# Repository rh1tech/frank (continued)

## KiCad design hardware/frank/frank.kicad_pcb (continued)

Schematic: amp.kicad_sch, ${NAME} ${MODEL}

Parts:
C25, C30, C35: 1u; C_0805_2012Metric
C26, C27, C28, C32, C33: 10u; C_0805_2012Metric
C29, C34: 100n; C_0805_2012Metric
C31: 10u; CP_Radial_D4.0mm_P1.50mm
C36: 100u; C_Radial_D6.3mm_P2.50mm
R50, R52: 2K; R_0805_2012Metric
R51, R53, R54, R55, R56, R57, R58, R61, R65: 10K; R_0805_2012Metric
R59, R60: 47K; R_0805_2012Metric
R62: 100R; R_0805_2012Metric
R63, R64: 20K; R_0805_2012Metric
U9: PAM8403D; SOP-16_P1.27mm; Mouser Part Number 700-MAX232CSE
U10: LM358; SO-8

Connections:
/AMP_L: C26.1, R51.1; also elsewhere on the board
/AMP_R: C27.1, R53.1; also elsewhere on the board
/Audio/AMP_OUTL: C32.2, R63.2; also elsewhere on the board
/Audio/AMP_OUTR: C33.2, R64.2; also elsewhere on the board
/Audio/AMP_PAM_OUTL_M: U9.3 (-OUTL); also elsewhere on the board
/Audio/AMP_PAM_OUTL_P: U9.1 (+OUT_L); also elsewhere on the board
/Audio/AMP_PAM_OUTR_M: U9.14 (-OUT_R); also elsewhere on the board
/Audio/AMP_PAM_OUTR_P: U9.16 (+OUT_R); also elsewhere on the board
/MONO_L: C25.1, R50.1, R51.2; also elsewhere on the board
/MONO_R: C30.1, R52.1, R53.2; also elsewhere on the board
/SHND: R65.2, U9.12 (SHND); also elsewhere on the board
GND: C28.1, C29.2, C31.2, C34.1, C35.2, C36.2, R50.2, R52.2, R55.1, R63.1, R64.1, U9.2 (PGND), U9.11 (GND), U9.15 (PGND), U10.4 (V-); also elsewhere on the board
unnamed: C25.2, R56.2
unnamed: C26.2, R57.2
unnamed: C27.2, R58.2
unnamed: C30.2, R61.2
unnamed: C32.1, R59.1, U10.7
unnamed: C33.1, R60.1, U10.1
unnamed: R56.1, U9.7 (INL)
unnamed: R61.1, U9.10 (INR)
unnamed: C29.1, U9.8 (VREF)
unnamed: C28.2, R54.1, R55.2, U10.3 (+), U10.5 (+)
unnamed: R58.1, R60.2, U10.2 (-)
unnamed: R57.1, R59.2, U10.6 (-)
unnamed: C31.1, C34.2, R54.2, R62.2, U10.8 (V+)
VBUS: C35.1, C36.1, R62.1, R65.1, U9.4 (PVDD), U9.5 (MUTE), U9.6 (VDD), U9.13 (PVDD); also elsewhere on the board

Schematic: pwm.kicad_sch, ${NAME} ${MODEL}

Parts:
C20, C21: 47n; C_0805_2012Metric
R39, R41: 10K; R_0805_2012Metric
R40, R42, R43, R44: 2K; R_0805_2012Metric
R45, R46: 1K; R_0805_2012Metric

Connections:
/PGPIO9: R43.1, R44.1; also elsewhere on the board
/PGPIO10: R46.2; also elsewhere on the board
/PGPIO11: R45.2; also elsewhere on the board
/PWM_L: R41.2, R42.1; also elsewhere on the board
/PWM_R: R39.2, R40.1; also elsewhere on the board
GND: C20.2, C21.2, R40.2, R42.2; also elsewhere on the board
unnamed: C20.1, R39.1, R43.2, R46.1
unnamed: C21.1, R41.1, R44.2, R45.1

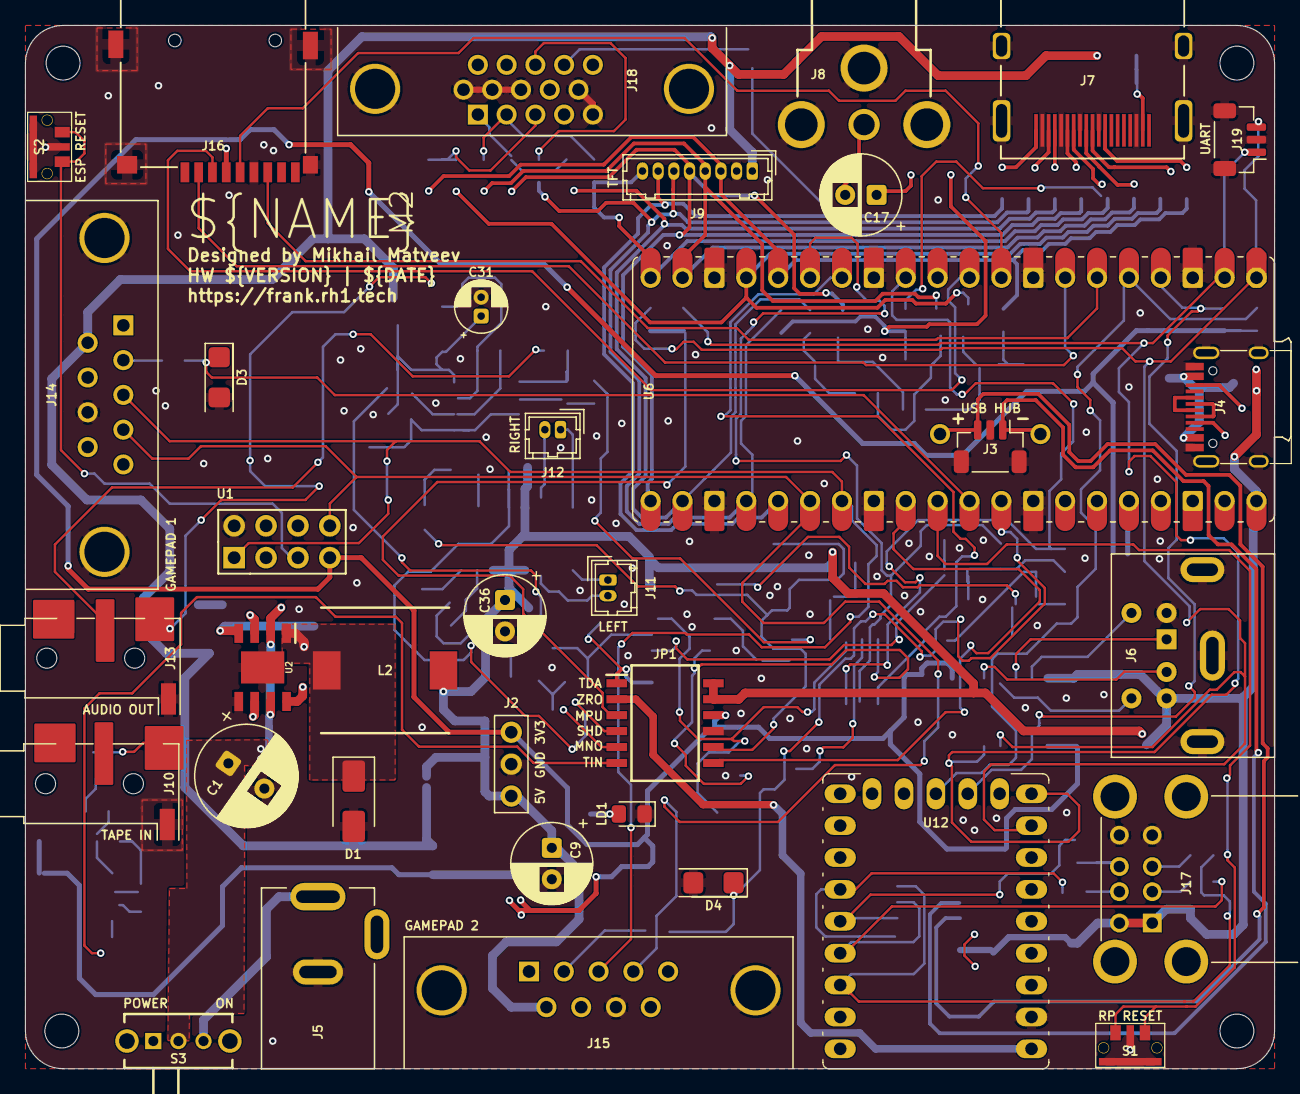
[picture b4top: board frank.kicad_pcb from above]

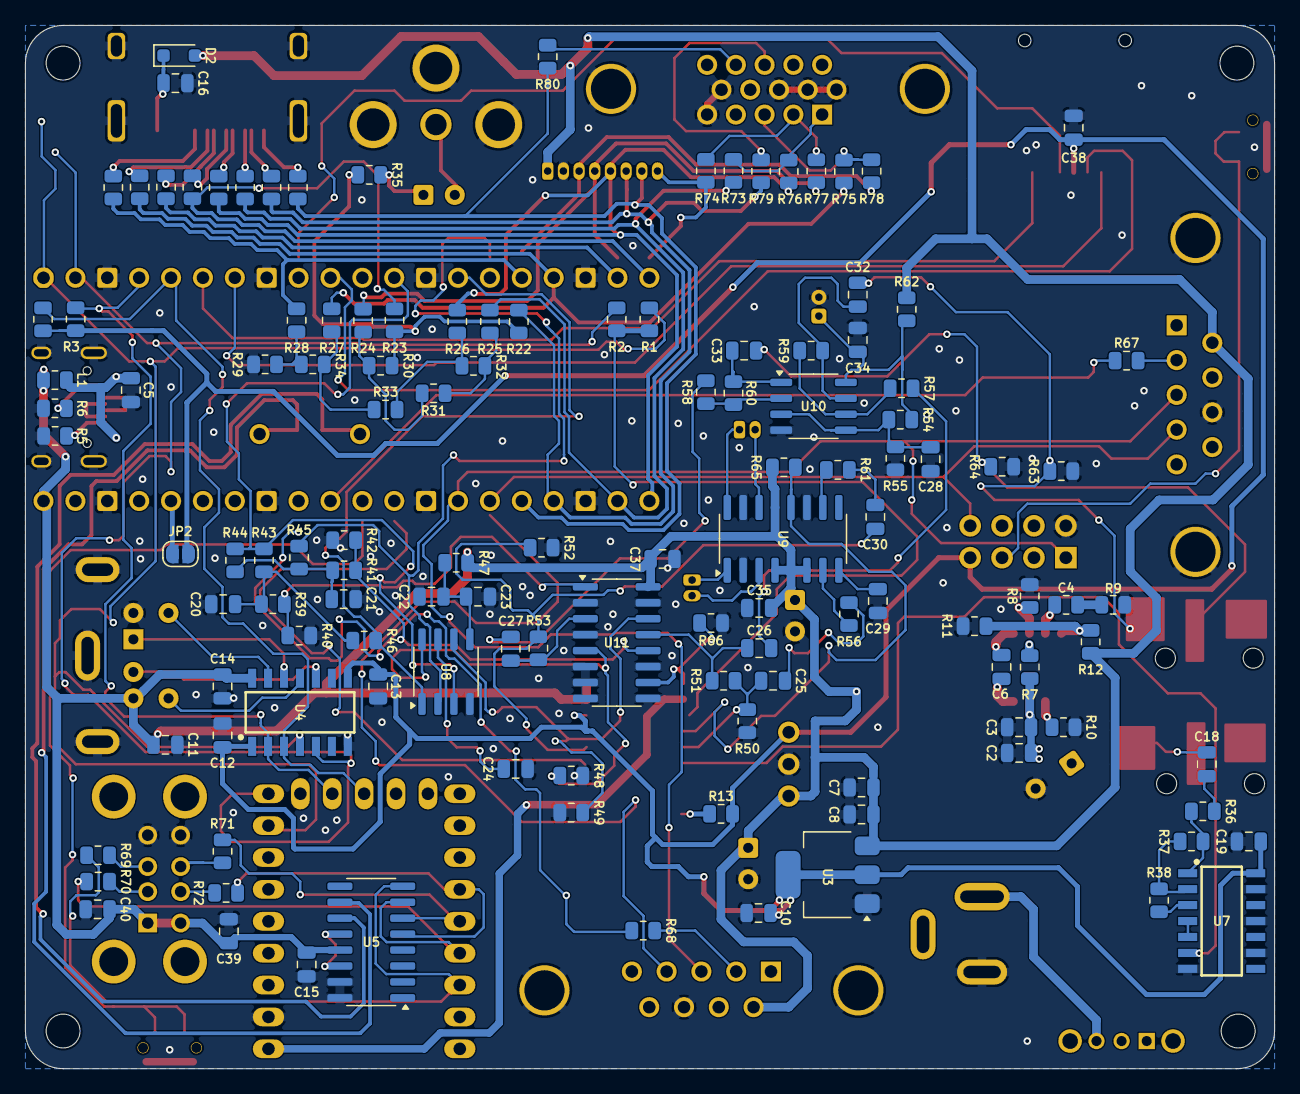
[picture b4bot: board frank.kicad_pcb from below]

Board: 2 copper layers, 99.5 x 83.1 mm, 166 parts (126 on the bottom side), 126 nets.

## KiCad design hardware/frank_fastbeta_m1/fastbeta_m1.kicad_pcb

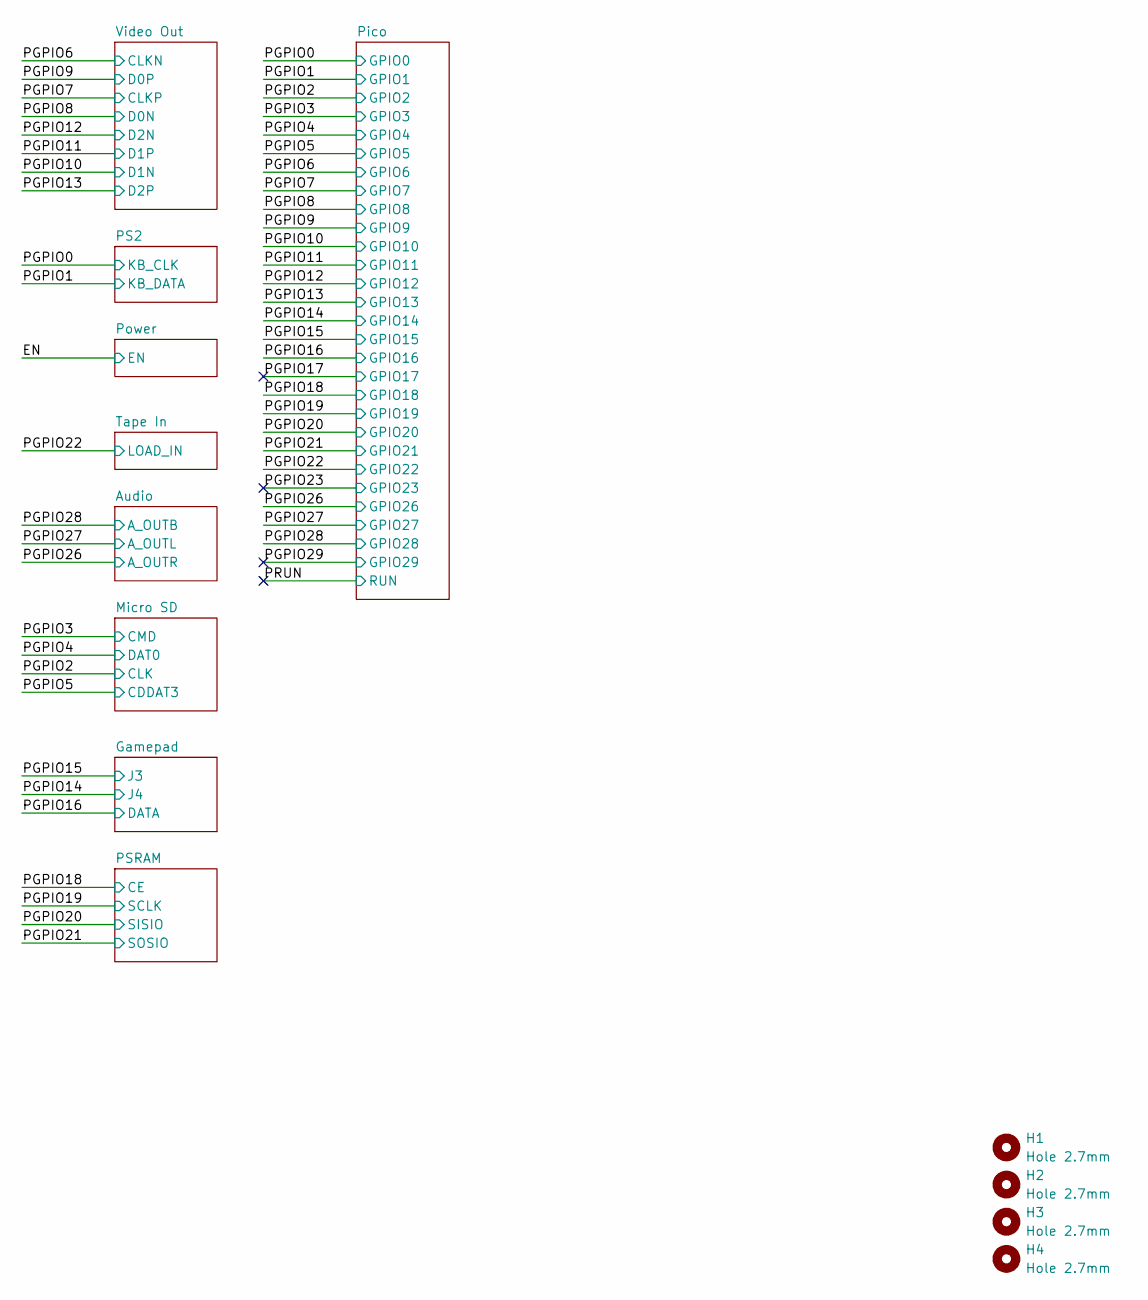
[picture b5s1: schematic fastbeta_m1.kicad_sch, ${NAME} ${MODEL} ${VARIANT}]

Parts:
H1, H2, H3, H4: Hole 2.7mm; Mounting Hole (2.7mm)

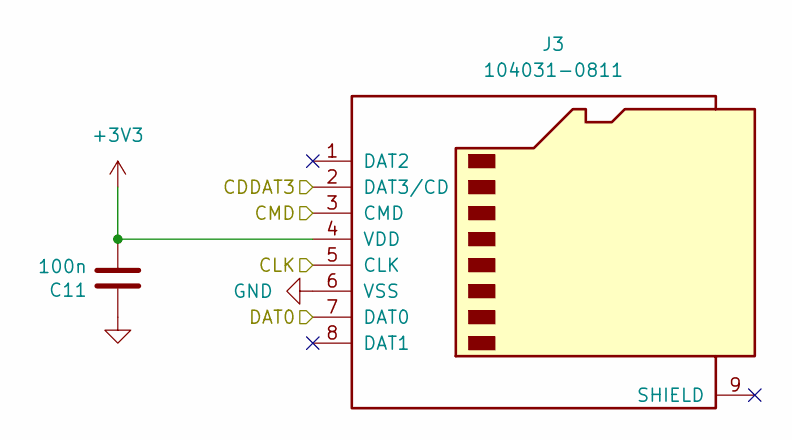
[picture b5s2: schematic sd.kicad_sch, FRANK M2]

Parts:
C11: 100n; Combined 0805 CR
J3: 104031-0811; MicroSD (SMD, long)

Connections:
+3V3: C11.2, J3.4 (VDD); also elsewhere on the board
/PGPIO2: J3.5 (CLK); also elsewhere on the board
/PGPIO3: J3.3 (CMD); also elsewhere on the board
/PGPIO4: J3.7 (DAT0); also elsewhere on the board
/PGPIO5: J3.2 (DAT3/CD); also elsewhere on the board
GND: C11.1, J3.6 (VSS); also elsewhere on the board

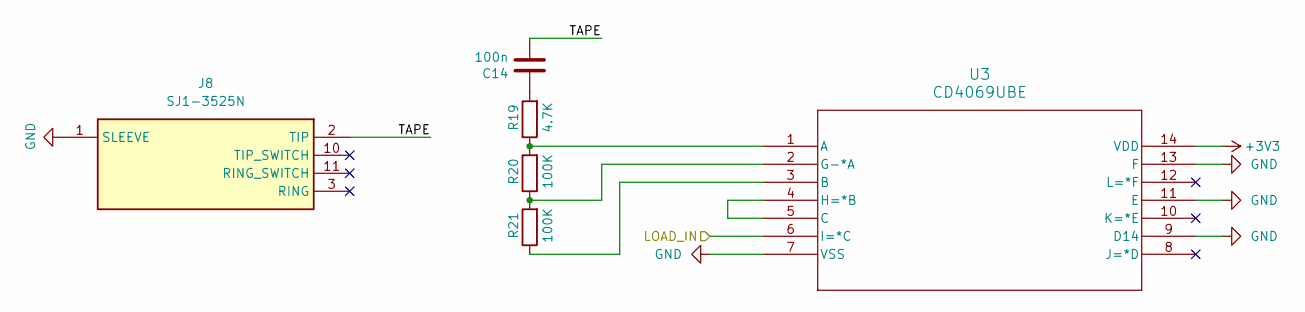
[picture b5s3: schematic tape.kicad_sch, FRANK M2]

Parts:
C14: 100n; Combined 0805 CR
J8: SJ1-3525N; SJ13525N; Mouser Part Number 490-SJ1-3525N
R19: 4.7K; Combined 0805 RE
R20, R21: 100K; Combined 0805 RE
U3: CD4069UBE

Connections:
+3V3: U3.14 (VDD); also elsewhere on the board
/PGPIO22: U3.6 (I=*C); also elsewhere on the board
/Tape In/TAPE: C14.2, J8.2 (TIP)
GND: J8.1 (SLEEVE), U3.7 (VSS), U3.9 (D14), U3.11 (E), U3.13 (F); also elsewhere on the board
unnamed: C14.1, R19.2
unnamed: R19.1, R20.2, U3.1 (A)
unnamed: R21.1, U3.3 (B)
unnamed: U3.4 (H=*B), U3.5 (C)
unnamed: R20.1, R21.2, U3.2 (G-*A)

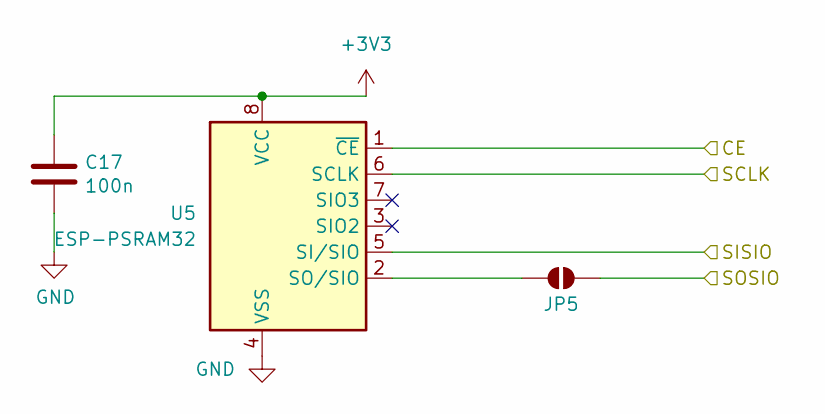
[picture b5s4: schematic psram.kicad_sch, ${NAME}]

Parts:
C17: 100n; Combined 0805 CR
JP5: Jumper (Solder); Jumper (solder)
U5: ESP-PSRAM32; SO-8

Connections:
+3V3: C17.1, U5.8 (VCC); also elsewhere on the board
/PGPIO18: U5.1 (~CE); also elsewhere on the board
/PGPIO19: U5.6 (SCLK); also elsewhere on the board
/PGPIO20: U5.5 (SI/SIO); also elsewhere on the board
/PGPIO21: JP5.2 (B); also elsewhere on the board
GND: C17.2, U5.4 (VSS); also elsewhere on the board
unnamed: JP5.1 (A), U5.2 (SO/SIO)

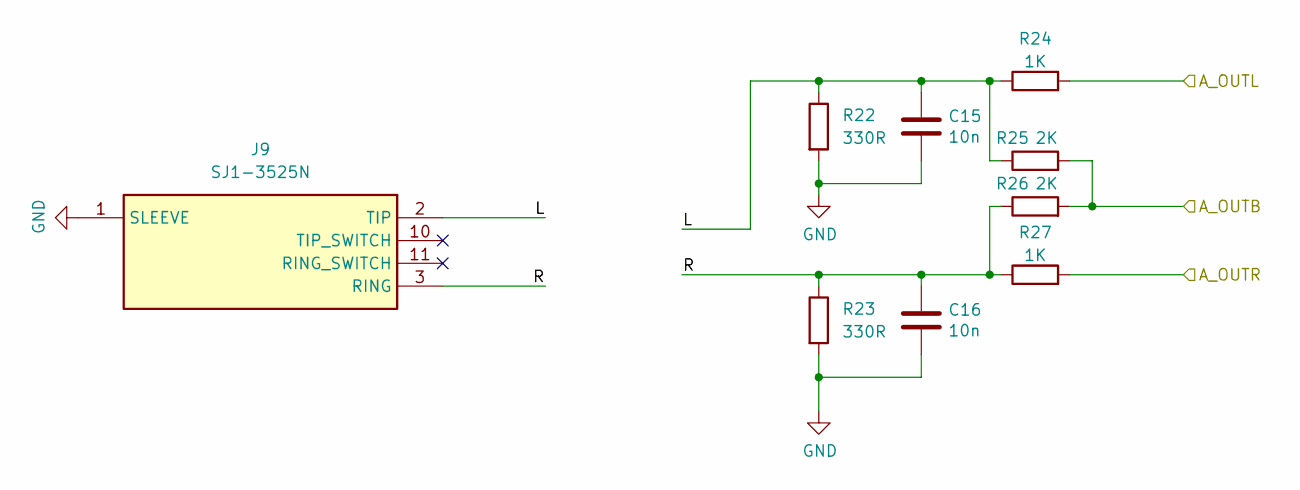
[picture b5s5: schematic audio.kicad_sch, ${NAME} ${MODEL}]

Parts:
C15, C16: 10n; Combined 0805 CR
J9: SJ1-3525N; SJ13525N; Mouser Part Number 490-SJ1-3525N
R22, R23: 330R; Combined 0805 RE
R24, R27: 1K; Combined 0805 RE
R25, R26: 2K; Combined 0805 RE

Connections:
/Audio/L: C15.1, J9.2 (TIP), R22.1, R24.1, R25.1
/Audio/R: C16.1, J9.3 (RING), R23.1, R26.1, R27.1
/PGPIO26: R27.2; also elsewhere on the board
/PGPIO27: R24.2; also elsewhere on the board
/PGPIO28: R25.2, R26.2; also elsewhere on the board
GND: C15.2, C16.2, J9.1 (SLEEVE), R22.2, R23.2; also elsewhere on the board

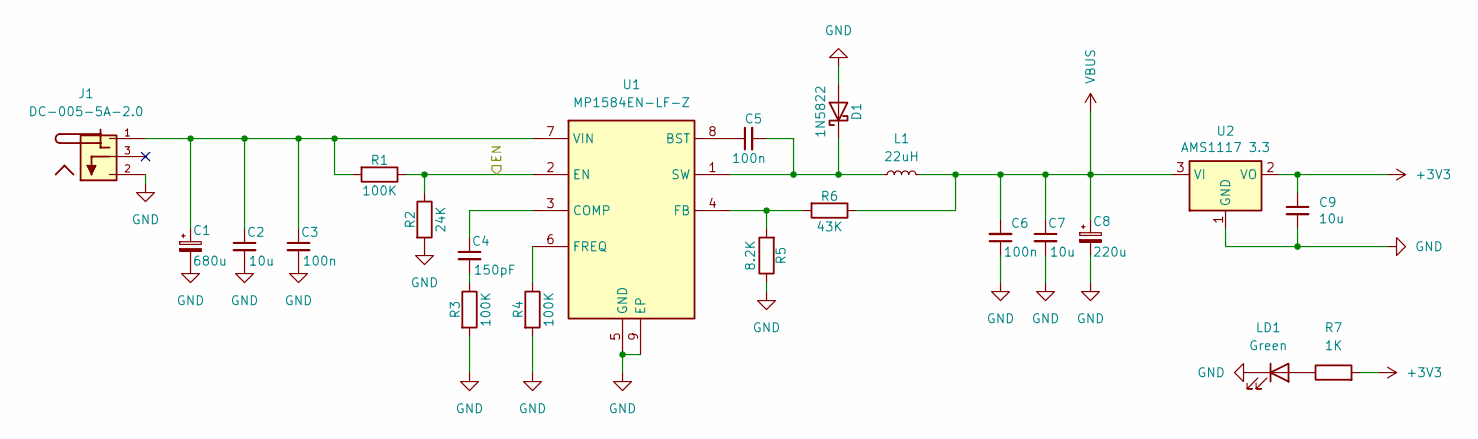
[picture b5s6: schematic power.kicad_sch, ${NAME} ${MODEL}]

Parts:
C1: 680u; Capacitor (Radial_D8.0mm_P3.50mm)
C2, C7, C9: 10u; Combined 0805 CR
C3, C5, C6: 100n; Combined 0805 CR
C4: 150pF; Combined 0805 CR
C8: 220u; Capacitor (Radial_D6.3mm_P2.50mm)
D1: 1N5822; D_DO-201AD_P5.08mm_Vertical_AnodeUp
J1: DC-005-5A-2.0; XKB_DC-005-5A-2.0; PARTREV A0
L1: 22uH; L_Radial_D9.5mm_P5.00mm_Fastron_07HVP
LD1: Green; Combined 0805 LD
R1, R3, R4: 100K; Combined 0805 RE
R2: 24K; Combined 0805 RE
R5: 8.2K; Combined 0805 RE
R6: 43K; Combined 0805 RE
R7: 1K; Combined 0805 RE
U1: MP1584EN-LF-Z; SOIC127P600X170-9N; Mouser Part Number 946-MP1584ENLFZ
U2: AMS1117 3.3; SOT-223

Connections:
+3V3: C9.1, R7.2, U2.2 (VO); also elsewhere on the board
/EN: R1.1, R2.1, U1.2 (EN)
GND: C1.2, C2.2, C3.2, C6.1, C7.2, C8.2, C9.2, D1.2 (A), J1.2, LD1.1 (K), R2.2, R3.2, R4.2, R5.1, U1.5 (GND), U1.9 (EP), U2.1 (GND); also elsewhere on the board
unnamed: C4.2, R3.1
unnamed: C5.2, D1.1 (K), L1.1, U1.1 (SW)
unnamed: LD1.2 (A), R7.1
unnamed: C5.1, U1.8 (BST)
unnamed: C4.1, U1.3 (COMP)
unnamed: R5.2, R6.2, U1.4 (FB)
unnamed: R4.1, U1.6 (FREQ)
unnamed: C1.1, C2.1, C3.1, J1.1, R1.2, U1.7 (VIN)
VBUS: C6.2, C7.1, C8.1, L1.2, R6.1, U2.3 (VI); also elsewhere on the board

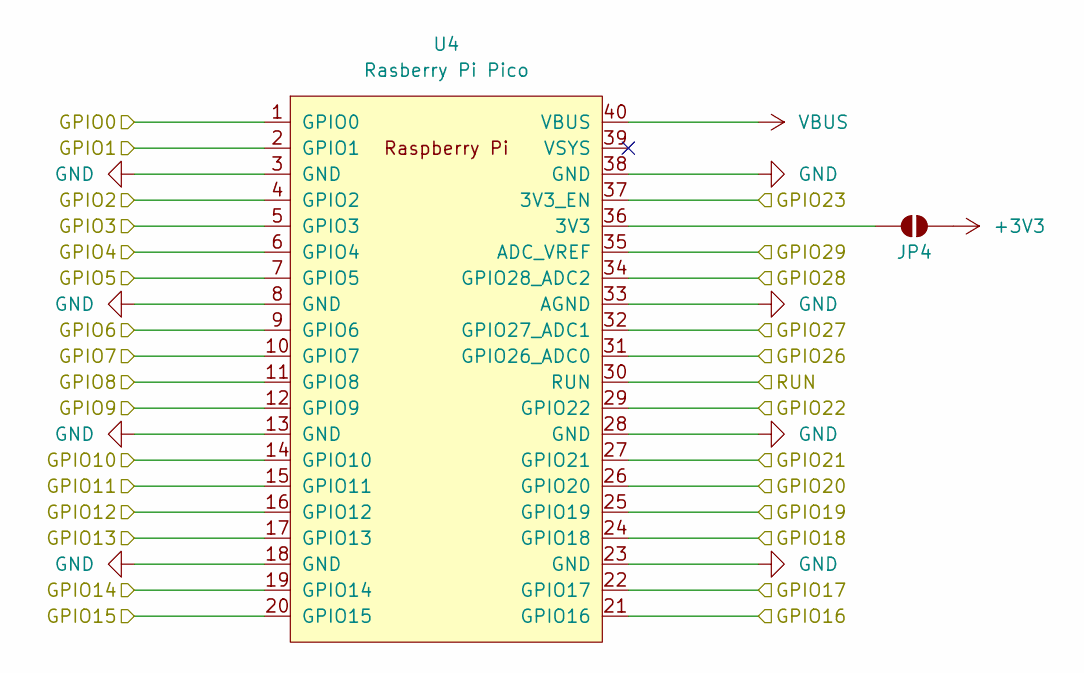
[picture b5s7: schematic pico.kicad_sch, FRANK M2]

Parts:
JP4: Jumper (Solder); Jumper (solder)
U4: Rasberry Pi Pico; Raspberry Pi Pico

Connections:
+3V3: JP4.2 (B); also elsewhere on the board
/PGPIO0: U4.1 (GPIO0); also elsewhere on the board
/PGPIO1: U4.2 (GPIO1); also elsewhere on the board
/PGPIO2: U4.4 (GPIO2); also elsewhere on the board
/PGPIO3: U4.5 (GPIO3); also elsewhere on the board
/PGPIO4: U4.6 (GPIO4); also elsewhere on the board
/PGPIO5: U4.7 (GPIO5); also elsewhere on the board
/PGPIO6: U4.9 (GPIO6); also elsewhere on the board
/PGPIO7: U4.10 (GPIO7); also elsewhere on the board
/PGPIO8: U4.11 (GPIO8); also elsewhere on the board
/PGPIO9: U4.12 (GPIO9); also elsewhere on the board
/PGPIO10: U4.14 (GPIO10); also elsewhere on the board
/PGPIO11: U4.15 (GPIO11); also elsewhere on the board
/PGPIO12: U4.16 (GPIO12); also elsewhere on the board
/PGPIO13: U4.17 (GPIO13); also elsewhere on the board
/PGPIO14: U4.19 (GPIO14); also elsewhere on the board
/PGPIO15: U4.20 (GPIO15); also elsewhere on the board
/PGPIO16: U4.21 (GPIO16); also elsewhere on the board
/PGPIO17: U4.22 (GPIO17)
/PGPIO17_1: U4.22 (GPIO17)
/PGPIO18: U4.24 (GPIO18); also elsewhere on the board
/PGPIO19: U4.25 (GPIO19); also elsewhere on the board
/PGPIO20: U4.26 (GPIO20); also elsewhere on the board
/PGPIO21: U4.27 (GPIO21); also elsewhere on the board
/PGPIO22: U4.29 (GPIO22); also elsewhere on the board
/PGPIO23: U4.37 (3V3_EN)
/PGPIO23_1: U4.37 (3V3_EN)
/PGPIO26: U4.31 (GPIO26_ADC0); also elsewhere on the board
/PGPIO27: U4.32 (GPIO27_ADC1); also elsewhere on the board
/PGPIO28: U4.34 (GPIO28_ADC2); also elsewhere on the board
/PGPIO29: U4.35 (ADC_VREF)
/PGPIO29_1: U4.35 (ADC_VREF)
/PRUN: U4.30 (RUN)
/PRUN_1: U4.30 (RUN)
GND: U4.3 (GND), U4.8 (GND), U4.13 (GND), U4.18 (GND), U4.23 (GND), U4.28 (GND), U4.33 (AGND), U4.38 (GND); also elsewhere on the board
unnamed: JP4.1 (A), U4.36 (3V3)
VBUS: U4.40 (VBUS); also elsewhere on the board

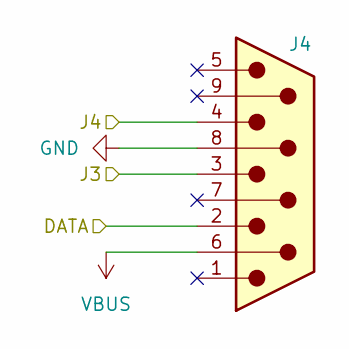
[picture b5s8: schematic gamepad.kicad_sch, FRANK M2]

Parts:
J4: D-SUB 9 Male; D-SUB (9 pin, male, top mount)

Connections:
/PGPIO14: J4.4; also elsewhere on the board
/PGPIO15: J4.3; also elsewhere on the board
/PGPIO16: J4.2; also elsewhere on the board
GND: J4.8; also elsewhere on the board
VBUS: J4.6; also elsewhere on the board

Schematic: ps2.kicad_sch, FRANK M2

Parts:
C10: 100n; Combined 0805 CR
J2: MDC-036; MiniDIN (6 Pin, female)
R8, R9: 1K; Combined 0805 RE

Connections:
+3V3: R8.2, R9.2; also elsewhere on the board
/PGPIO0: J2.5, R8.1; also elsewhere on the board
/PGPIO1: J2.1, R9.1; also elsewhere on the board
GND: C10.2, J2.3; also elsewhere on the board
VBUS: C10.1, J2.4; also elsewhere on the board

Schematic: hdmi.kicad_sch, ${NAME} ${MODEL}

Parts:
C12: 100n; Combined 0805 CR
C13: 470pF; Combined 0805 CR
D2: 1N5819; Diode (SOD81 P2.54mm Vertical AnodeUp)
J5: DC3RX19JA2; HDMI (female)
J6: D-SUB 15 Female; D-SUB (15 pin, female)
J7: RCA-103; RCA
JP1, JP2, JP3: Jumper (Solder); Jumper (solder)
R10, R11, R12, R13, R14, R15, R16, R17: 220R; Combined 0805 RE
R18: 75R; Combined 0805 RE

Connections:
/PGPIO6: R10.2; also elsewhere on the board
/PGPIO7: R11.2; also elsewhere on the board
/PGPIO8: R12.2; also elsewhere on the board
/PGPIO9: R13.2; also elsewhere on the board
/PGPIO10: R14.2; also elsewhere on the board
/PGPIO11: R15.2; also elsewhere on the board
/PGPIO12: R16.2; also elsewhere on the board
/PGPIO13: R17.2, R18.1; also elsewhere on the board
/Video Out/VGA_B: J5.12 (CLKN), J6.3, JP1.1 (A), R10.1
/Video Out/VGA_BH: J5.10 (CLKP), JP1.2 (B), R11.1
/Video Out/VGA_G: J5.9 (D0N), J6.2, JP2.1 (A), R12.1
/Video Out/VGA_GH: J5.7 (D0P), JP2.2 (B), R13.1
/Video Out/VGA_HS: J5.3 (D2N), J6.13, R16.1
/Video Out/VGA_R: J5.6 (D1N), J6.1, JP3.1 (A), R14.1
/Video Out/VGA_RH: J5.4 (D1P), JP3.2 (B), R15.1
/Video Out/VGA_VS: J5.1 (D2P), J6.14, R17.1
GND: C12.2, C13.2, J5.2 (G_D2), J5.5 (G_D1), J5.8 (G_D0), J5.11 (G_CLK), J5.17 (G_DDC/CEC), J5.20 (SHIELD1), J5.21 (SHIELD2), J5.22 (SHIELD3), J5.23 (SHIELD4), J6.0, J6.5, J6.6, J6.7, J6.8, J6.10, J7.2; also elsewhere on the board
unnamed: C12.1, D2.1 (K), J5.18 (+5V)
unnamed: C13.1, J7.1, R18.2
VBUS: D2.2 (A); also elsewhere on the board

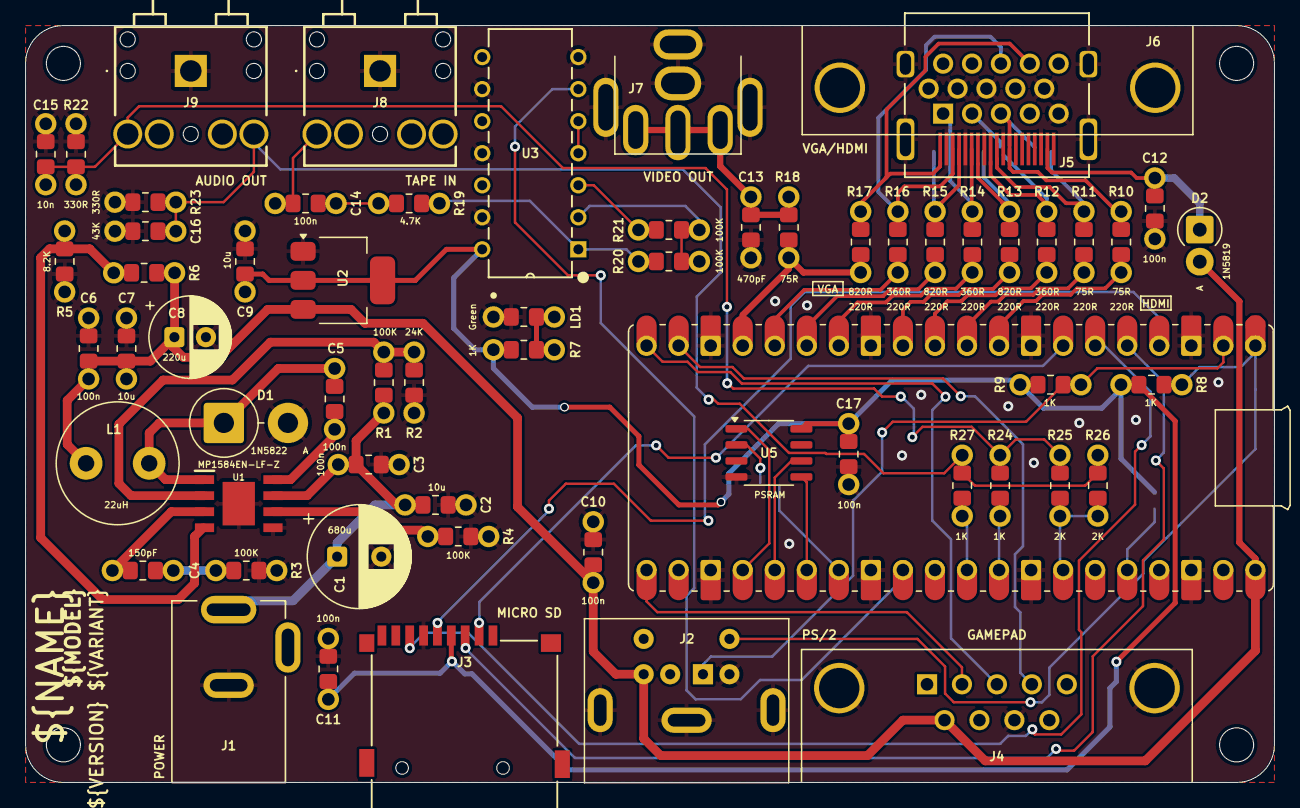
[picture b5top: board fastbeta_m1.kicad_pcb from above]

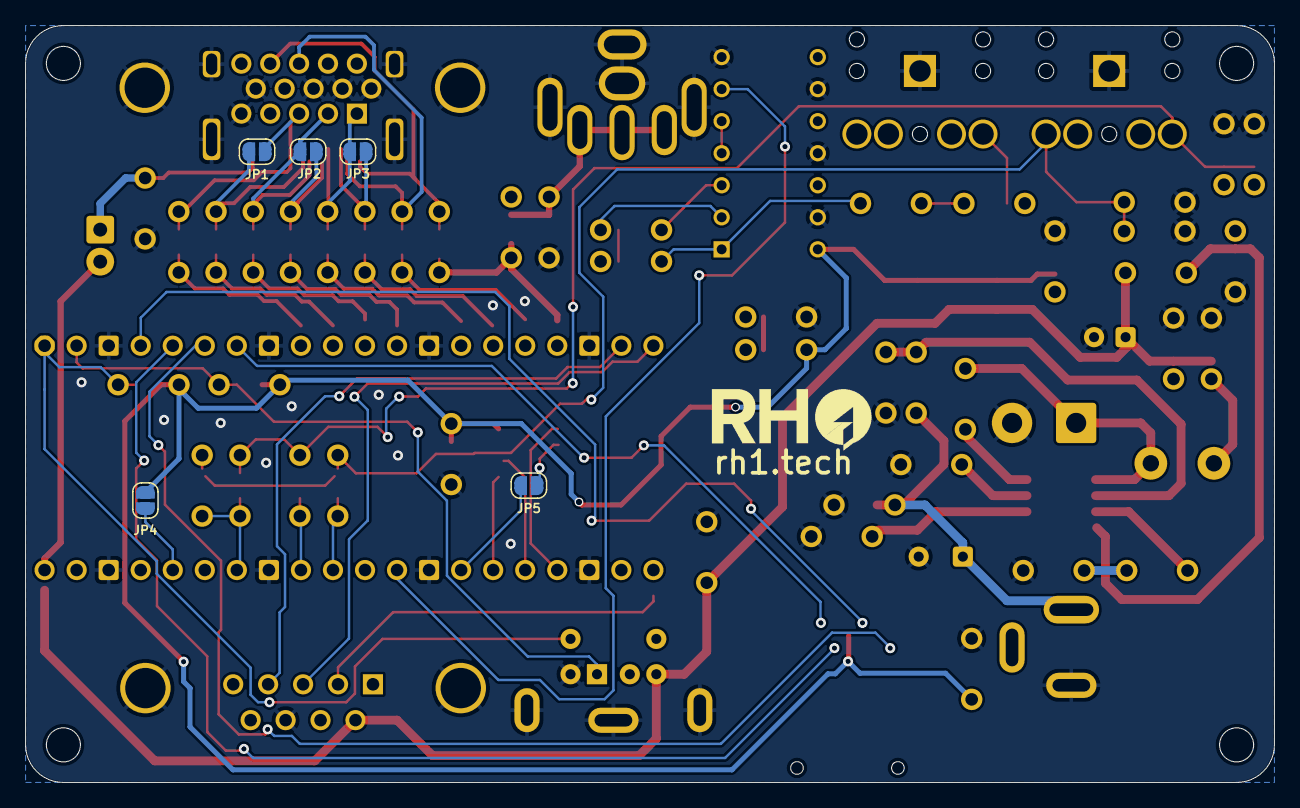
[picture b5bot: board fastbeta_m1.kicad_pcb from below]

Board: 2 copper layers, 99.0 x 60.0 mm, 71 parts (5 on the bottom side), 57 nets.

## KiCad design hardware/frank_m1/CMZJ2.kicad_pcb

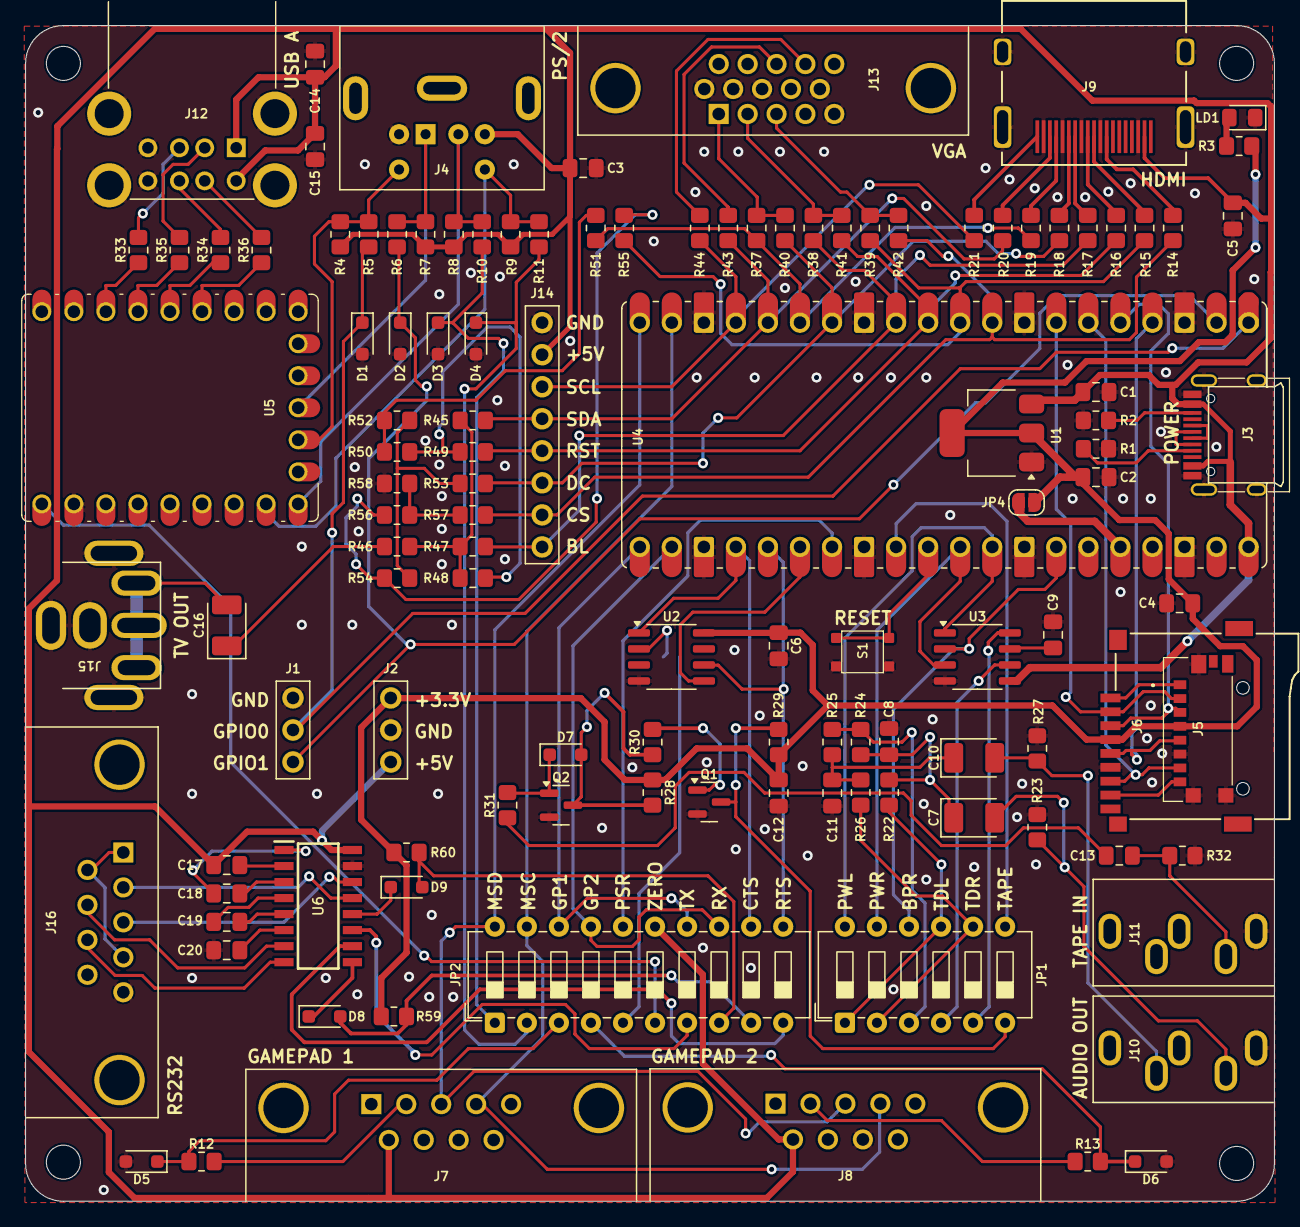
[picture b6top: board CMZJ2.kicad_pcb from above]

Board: 2 copper layers, 99.0 x 93.2 mm, 123 parts (1 on the bottom side), 113 nets.

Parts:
C1, C2, C9, C14, C15: 10u; Capacitor (0805)
C3, C4, C5, C6, C12, C13: 100n; Capacitor (0805)
C7, C10: 10u; Capacitor (3528, tantalum, polar)
C8, C11: 10n; Capacitor (0805)
C16: 220u; Capacitor (3528, tantalum, polar)
C17, C18, C19, C20: 1u; Capacitor (0805)
D1, D2, D3, D4, D5, D6: 3V3; Diode (SOD-323)
D7, D8, D9: 1N4148; Diode (SOD-323)
H1, H2, H3, H4: Hole 2.7mm; Mounting Hole (2.7mm)
J1, J2: Pin Header 1x03; Pin Header (1x03)
J3: USB4215; USB Type C
J4: MDC-036; MiniDIN (6 Pin, female)
J5: 0475710001; MicroSD (SMD, short)
J6: 104031-0811; MicroSD (SMD, long)
J7, J8, J16: D-SUB 9 Male; D-SUB (9 pin, male, top mount)
J9: DC3RX19JA2; HDMI (female)
J10, J11: SJ1-353XNG; Jack (3.5mm)
J12: SS-52100-004; USB Type A (stacked)
J13: D-SUB 15 Female; D-SUB (15 pin, female)
J14: Pin Header 1x08; Pin Header (1x08)
J15: RCA-103; RCA
JP1: SW_DIP_x06; DIP Switch (6)
JP2: SW_DIP_x10; DIP Switch (10)
JP3, JP4: Jumper (Solder); Jumper (solder)
LD1: Green; LED (0805)
Q1, Q2: BC850; SOT-23
R1, R2: 5.1K; Resistor (0805)
R3, R4, R7, R8, R9, R12, R13, R22, R26, R29, R40, R41, R42, R59, R60: 1K; Resistor (0805)
R5, R6, R10, R11, R32, R43, R44: 100R; Resistor (0805)
R14, R15, R16, R17, R18, R19, R20, R21, R47, R49, R51, R53, R55, R57: 270R; Resistor (0805)
R23, R27, R37, R38, R39: 330R; Resistor (0805)
R24, R25: 2K; Resistor (0805)
R28, R30, R31: 10K; Resistor (0805)
R33, R34, R35, R36: 22R; Resistor (0805)
R45: 750R; Resistor (0805)
R46: 51R; Resistor (0805)
R48, R50, R52, R54, R56: 150R; Resistor (0805)
R58: 300R; Resistor (0805)
S1: TS-1233; Button (SMD, 3x3mm, 1-1)
U1: NCP1117 3.3; SOT-223
U2: ESP-PSRAM32; SO-8
U3: TDA1387T; SO-8
U4: Rasberry Pi Pico; Raspberry Pi Pico
U5: RP2040-Zero; Raspberry Pi Zero
U6: MAX232CSE+; SOIC127P600X175-16N

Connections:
+3V3: C2.1, C4.2, C6.1, C12.1, J2.1, J5.P4 (VDD), J6.4 (VDD), JP4.2 (B), R3.2, R28.1, R29.1, R59.2, R60.2, U1.2 (VO), U2.8 (VCC)
/A_OUTB: JP1.3, R24.2, R25.2
/A_OUTL: JP1.1, JP1.9, R22.2
/A_OUTR: JP1.2, JP1.8, R26.2
/A_TDAL: JP1.4, U3.6 (A_LEFT)
/A_TDAR: JP1.5, U3.8 (A_RIGHT)
/Audio Out/L: C7.2, J10.T, R23.1
/Audio Out/R: C10.2, J10.R, R27.1
/Composite/CVBS: C16.2, J15.1
/GP1_DATA: D5.1 (K), JP2.3, R12.1
/GP2_DATA: D6.1 (K), JP2.4, R13.1
/GPIO0: D1.1 (K), J1.2, R5.2, U4.1 (GPIO0)
/GPIO1: D2.1 (K), J1.3, R6.2, U4.2 (GPIO1)
/GPIO2: J5.P5 (CLK), J6.5 (CLK), U4.4 (GPIO2)
/GPIO3: J5.P3 (CMD), J6.3 (CMD), U4.5 (GPIO3)
/GPIO4: J5.P7 (DAT0), J6.7 (DAT0), U4.6 (GPIO4)
/GPIO5: J5.P2 (CD/DAT3), J6.2 (DAT3/CD), U4.7 (GPIO5)
/GPIO6: J14.7, R14.2, R42.1, R57.1, U4.9 (GPIO6)
/GPIO7: R15.2, R39.1, R55.1, U4.10 (GPIO7)
/GPIO8: J14.5, R16.2, R41.1, R49.1, U4.11 (GPIO8)
/GPIO9: J14.8, R17.2, R38.1, R47.1, U4.12 (GPIO9)
/GPIO10: J14.6, R18.2, R40.1, R53.1, U4.14 (GPIO10)
/GPIO11: R19.2, R37.1, R51.1, U4.15 (GPIO11)
/GPIO12: J14.4, R20.2, R43.2, R45.1, U4.16 (GPIO12)
/GPIO13: J14.3, R21.2, R44.2, U4.17 (GPIO13)
/GPIO14: J7.4, J8.4, JP2.19, U4.19 (GPIO14)
/GPIO15: J7.3, J8.3, JP2.20, U4.20 (GPIO15)
/GPIO16: JP2.14, JP2.18, U4.21 (GPIO16)
/GPIO17: JP2.13, JP2.17, U4.22 (GPIO17)
/GPIO18: JP2.12, U2.1 (~CE), U4.24 (GPIO18)
/GPIO19: JP2.11, U2.6 (SCLK), U4.25 (GPIO19)
/GPIO20: U2.5 (SI/SIO), U4.26 (GPIO20)
/GPIO21: JP2.16, U4.27 (GPIO21)
/GPIO22: JP1.7, U4.29 (GPIO22)
/GPIO26: JP1.11, U3.3 (DATA), U4.31 (GPIO26_ADC0)
/GPIO27: JP1.12, U3.1 (SCLK), U4.32 (GPIO27_ADC1)
/GPIO28: JP1.10, U3.2 (LRCK), U4.34 (GPIO28_ADC2)
/KB_CLK: J4.5, R4.2, R5.1, U5.13 (12)
/KB_DATA: J4.1, R6.1, R7.2, U5.12 (11)
/LOAD_IN_D: JP1.6, Q1.3 (C), R29.2
/MS_CLK: J4.6, R9.2, R11.1, U5.16 (15)
/MS_CLK_3V: D4.1 (K), JP2.2, R11.2
/MS_DATA: J4.2, R8.2, R10.1, U5.15 (14)
/MS_DATA_3V: D3.1 (K), JP2.1, R10.2
/Micro SD/DAT1: J5.P8 (DAT1), J6.8 (DAT1)
/Micro SD/DAT2: J5.P1 (DAT2), J6.1 (DAT2)
/PSR_SOSIO: JP2.5, JP3.2 (B)
/Power/D+: J3.6 (DP1), J3.8 (DP2)
/Power/D-: J3.5 (DN2), J3.7 (DN1)
/RS232/C1+: C18.2, U6.1 (C1+)
/RS232/C1-: C18.1, U6.3 (C1-)
/RS232/C2+: C19.2, U6.4 (C2+)
/RS232/C2-: C19.1, U6.5 (C2-)
/RS232/CTS_IN: J16.7, U6.7 (T2OUT)
/RS232/CTS_MAX: D8.1 (K), U6.9 (R2OUT)
/RS232/RTS_IN: J16.8, U6.8 (R2IN)
/RS232/RX_IN: J16.3, U6.14 (T1OUT)
/RS232/RX_MAX: D9.1 (K), U6.12 (R1OUT)
/RS232/TX_IN: J16.2, U6.13 (R1IN)
/RS232/V+: C17.1, U6.2 (V+)
/RS232/V-: C20.1, U6.6 (V-)
/RS232_CTS: D8.2 (A), JP2.9, R59.1
/RS232_RTS: JP2.10, U6.10 (T2IN)
/RS232_RX: D9.2 (A), JP2.8, R60.1
/RS232_TX: JP2.7, U6.11 (T1IN)
/RUN: S1.1, U4.30 (RUN)
/USB_D1M: R35.1, U5.4 (3)
/USB_D1P: R33.1, U5.3 (2)
/USB_D2M: R36.1, U5.6 (5)
/USB_D2P: R34.1, U5.5 (4)
/ZERO_VBUS: JP2.6, U5.23 (5V)
GND: C1.2, C2.2, C3.2, C4.1, C5.2, C6.2, C8.2, C9.2, C11.2, C12.2, C14.2, C15.2, C20.2, D1.2 (A), D2.2 (A), D3.2 (A), D4.2 (A), D5.2 (A), D6.2 (A), J1.1, J2.2, J3.1 (GND), J3.12 (GND), J3.13 (SHIELD), J4.3, J5.G1 (GND_1), J5.G2 (GND_2), J5.G3 (GND_3), J5.P6 (VSS), J6.6 (VSS), J7.8, J8.8, J9.2 (G_D2), J9.5 (G_D1), J9.8 (G_D0), J9.11 (G_CLK), J9.17 (G_DDC/CEC), J9.20 (SHIELD1), J9.21 (SHIELD2), J9.22 (SHIELD3), J9.23 (SHIELD4), J10.S, J11.S, J12.4 (GND1), J12.8 (GND2), J12.9 (Shield), J13.0, J13.5, J13.6, J13.7, J13.8, J13.10, J14.1, J15.2, J16.5, LD1.1 (K), Q1.2 (E), Q2.2 (E), R1.1, R2.1, R23.2, R27.2, R32.2, R58.1, S1.2, U1.1 (GND), U2.4 (VSS), U3.4 (AGND), U4.3 (GND), U4.8 (GND), U4.13 (GND), U4.18 (GND), U4.23 (GND), U4.28 (GND), U4.33 (AGND), U4.38 (GND), U5.22 (GND), U6.15 (GND)
unnamed: C7.1, C8.1, R22.1, R24.1
unnamed: C10.1, C11.1, R25.1, R26.1
unnamed: C13.1, J11.T, R32.1
unnamed: C13.2, R31.1
unnamed: C16.1, R46.2
unnamed: D7.2 (A), Q2.3 (C), R28.2, R30.1
unnamed: D7.1 (K), Q2.1 (B), R31.2
unnamed: J3.4 (CC1), R1.2
unnamed: J3.10 (CC2), R2.2
unnamed: J7.2, R12.2
unnamed: J8.2, R13.2
unnamed: J9.12 (CLKN), R14.1
unnamed: J9.10 (CLKP), R15.1
unnamed: J9.9 (D0N), R16.1
unnamed: J9.7 (D0P), R17.1
unnamed: J9.6 (D1N), R18.1
unnamed: J9.4 (D1P), R19.1
unnamed: J9.3 (D2N), R20.1
unnamed: J9.1 (D2P), R21.1
unnamed: J12.3 (D1+), R33.2
unnamed: J12.2 (D1-), R35.2
unnamed: J12.7 (D2+), R34.2
unnamed: J12.6 (D2-), R36.2
unnamed: J13.1, R37.2, R40.2
unnamed: J13.2, R38.2, R41.2
unnamed: J13.3, R39.2, R42.2
unnamed: J13.13, R43.1
unnamed: J13.14, R44.1
unnamed: J16.1, J16.4, J16.6
unnamed: JP3.1 (A), U2.2 (SO/SIO)
unnamed: JP4.1 (A), U4.36 (3V3)
unnamed: LD1.2 (A), R3.1
unnamed: Q1.1 (B), R30.2
unnamed: R45.2, R46.1, R47.2, R48.2
unnamed: R48.1, R49.2, R50.2
unnamed: R50.1, R51.2, R52.2
unnamed: R52.1, R53.2, R54.2
unnamed: R54.1, R55.2, R56.2
unnamed: R56.1, R57.2, R58.2
unnamed: C9.1, U3.7 (FLT)
VBUS: C1.1, C3.1, C5.1, C14.1, C15.1, C17.2, J2.3, J3.2 (VBUS), J3.11 (VBUS), J4.4, J7.6, J8.6, J9.18 (+5V), J12.1 (VBUS1), J12.5 (VBUS2), J14.2, JP2.15, R4.1, R7.1, R8.1, R9.1, U1.3 (VI), U3.5 (VA), U4.40 (VBUS), U6.16 (VCC)
